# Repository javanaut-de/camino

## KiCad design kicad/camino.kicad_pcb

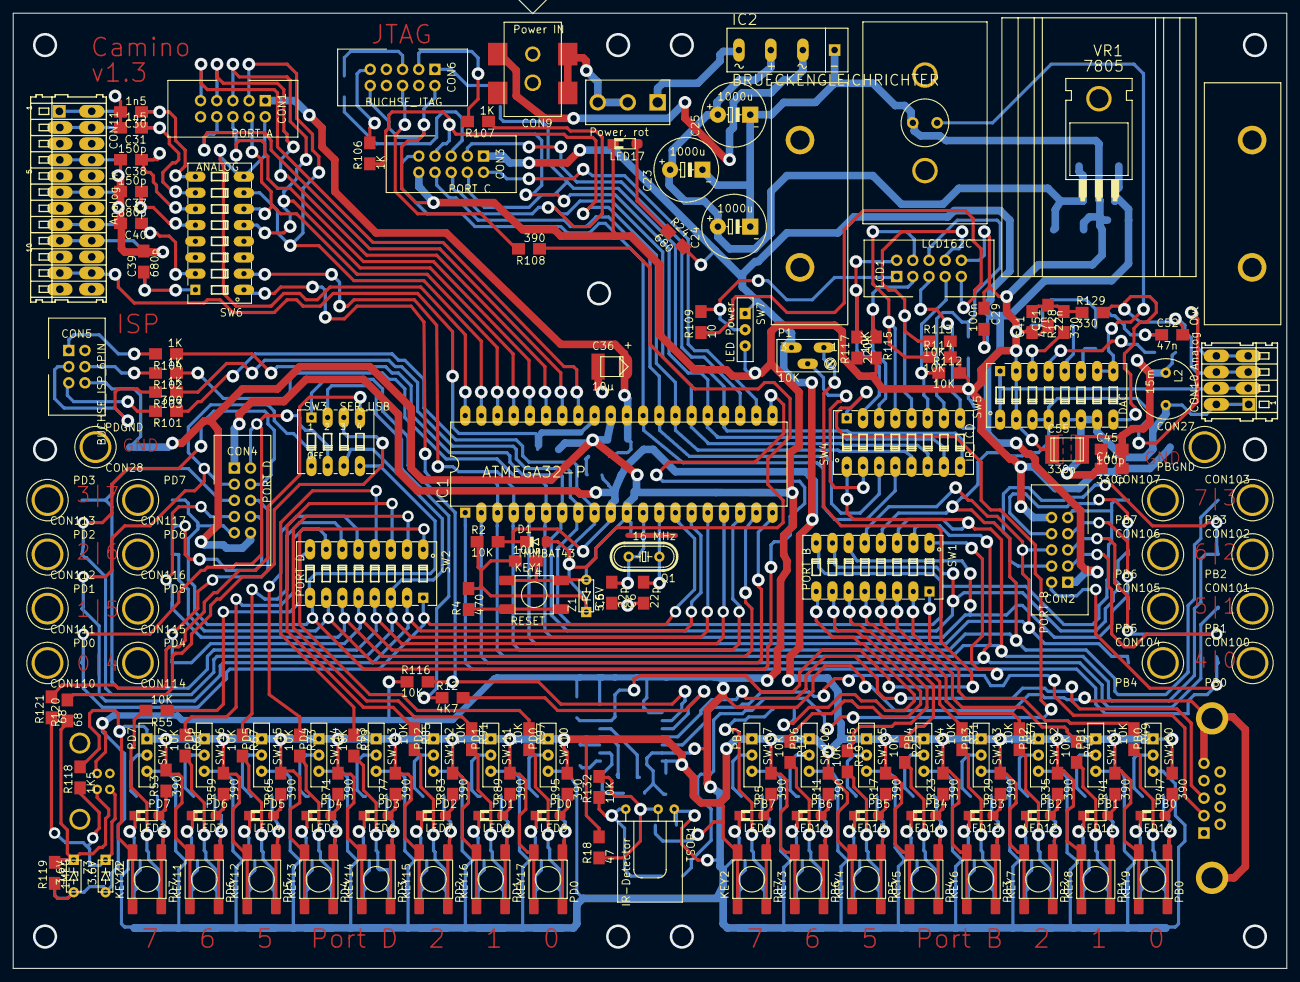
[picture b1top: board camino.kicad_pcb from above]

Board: 2 copper layers, 200.0 x 150.0 mm, 306 parts (0 on the bottom side), 216 nets.

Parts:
C1, C2, C3, C4, C26, C28, C29, C32, C33, C34, C35, C47: 100n; KONDENSATOR_SMD_1206
C5, C6: 22p; KONDENSATOR_SMD_1206
C7, C8, C9, C10, C11, C12, C13, C14, C15, C16, C17, C18, C19, C20, C21, C22: 220n; KONDENSATOR_SMD_1206
C23, C24, C25: 1000u; ELKO_RADIAL_11MM
C27, C46, C55: 330n; KONDENSATOR_SMD_1812
C30, C31: 1n5; KONDENSATOR_SMD_1206
C36: 10µ; ELKO_SMD_TM_B
C37, C38: 150p; KONDENSATOR_SMD_1206
C39, C40: 680p; KONDENSATOR_SMD_1206
C41, C52: 47n; KONDENSATOR_SMD_1206
C42, C51: 22n; KONDENSATOR_SMD_1206
C44: 330p; KONDENSATOR_SMD_1206
C45, C49, C50: 100p; KONDENSATOR_SMD_1206
CON1: PORT A; PFOSTENSTIFTLEISTE_10PIN
CON2: PORT B; PFOSTENSTIFTLEISTE_10PIN
CON3: PORT C; PFOSTENSTIFTLEISTE_10PIN
CON4: PORT D; PFOSTENSTIFTLEISTE_10PIN
CON5: BUCHSE_ISP_6PIN; PFOSTENSTIFTLEISTE_6PIN
CON6: BUCHSE_JTAG; PFOSTENSTIFTLEISTE_10PIN
CON7: RS232; BUCHSE_SERIELL_SUBD9_PIN
CON8: BUCHSE_USB_B; BUCHSE_USB_B_PIN
CON9: Power IN; BUCHSE_DC
CON10: Analog Out; KLEMMBUCHSE_WAGO_233_504_4PIN
CON11: Analog In; KLEMMBUCHSE_WAGO_233_512_12PIN
CON27: PBGND; BUCHSE_LABOR_2MM
CON28: PDGND; BUCHSE_LABOR_2MM
CON100: PB0; BUCHSE_LABOR_2MM
CON101: PB1; BUCHSE_LABOR_2MM
CON102: PB2; BUCHSE_LABOR_2MM
CON103: PB3; BUCHSE_LABOR_2MM
CON104: PB4; BUCHSE_LABOR_2MM
CON105: PB5; BUCHSE_LABOR_2MM
CON106: PB6; BUCHSE_LABOR_2MM
CON107: PB7; BUCHSE_LABOR_2MM
CON110: PD0; BUCHSE_LABOR_2MM
CON111: PD1; BUCHSE_LABOR_2MM
CON112: PD2; BUCHSE_LABOR_2MM
CON113: PD3; BUCHSE_LABOR_2MM
CON114: PD4; BUCHSE_LABOR_2MM
CON115: PD5; BUCHSE_LABOR_2MM
CON116: PD6; BUCHSE_LABOR_2MM
CON117: PD7; BUCHSE_LABOR_2MM
D1: TMMBAT43; DIODE_MINIMELF
D2: S4D; DIODE_SMD_DO214AB
IC1: ATMEGA32-P; DIL40
IC2: BRUECKENGLEICHRICHTER; GLEICHRICHTER_SIL4
IC3: MAX202SO16L; SO16L
KEY1: RESET; TASTER_LSG1301
KEY2: PB7; TASTER_LSG1301
KEY3: PB6; TASTER_LSG1301
KEY4: PB5; TASTER_LSG1301
KEY5: PB4; TASTER_LSG1301
KEY6: PB3; TASTER_LSG1301
KEY7: PB2; TASTER_LSG1301
KEY8: PB1; TASTER_LSG1301
KEY9: PB0; TASTER_LSG1301
KEY10: PD7; TASTER_LSG1301
KEY11: PD6; TASTER_LSG1301
KEY12: PD5; TASTER_LSG1301
KEY13: PD4; TASTER_LSG1301
KEY14: PD3; TASTER_LSG1301
KEY15: PD2; TASTER_LSG1301
KEY16: PD1; TASTER_LSG1301
KEY17: PD0; TASTER_LSG1301
L1: 10u; SPULE_SMD_1008
L2: 15m; SPULE_RADIAL_200MIL
LCD1: LCD162C; LCD_PULT_162C_BC
LED1: PB7; LED_KINGBRIGHT
LED2: PD7; LED_KINGBRIGHT
LED3: PD6; LED_KINGBRIGHT
LED4: PD5; LED_KINGBRIGHT
LED5: PD4; LED_KINGBRIGHT
LED6: PD3; LED_KINGBRIGHT
LED7: PD2; LED_KINGBRIGHT
LED8: PD1; LED_KINGBRIGHT
LED9: PD0; LED_KINGBRIGHT
LED10: PB0; LED_KINGBRIGHT
LED11: PB1; LED_KINGBRIGHT
LED12: PB2; LED_KINGBRIGHT
LED13: PB3; LED_KINGBRIGHT
LED14: PB4; LED_KINGBRIGHT
LED15: PB5; LED_KINGBRIGHT
LED16: PB6; LED_KINGBRIGHT
LED17: Power, rot; LED_KINGBRIGHT
P1: 10K; 3296Y
Q1: 16 MHz; HC49U
R1: 4R7; WIDERSTAND_SMD_1206
R2, R7, R10, R13, R16, R19, R22, R25, R28, R31, R34, R37, R40, R43, R46, R49, R52, R55, R58, R61, R64, R67, R70, R73, R76, R79, R82, R85, R88, R91, R94, R97, R100, R110, R111, R112, R113, R114, R115, R116, R122, R123, R124, R125, R132: 10K; WIDERSTAND_SMD_1206
R3, R6, R102, R103, R104, R105, R106, R107: 1K; WIDERSTAND_SMD_1206
R4: 470; WIDERSTAND_SMD_1206
R5, R11, R17, R23, R29, R35, R41, R47, R53, R59, R65, R71, R77, R83, R89, R95, R101, R108: 390; WIDERSTAND_SMD_1206
R8, R14, R20, R26, R30, R32, R36, R38, R42, R44, R48, R50, R54, R56, R60, R62, R66, R68, R72, R74, R78, R80, R84, R86, R90, R92, R96, R98, R133, R134, R135, R136: 470K; WIDERSTAND_SMD_1206
R9, R15, R21, R27, R33, R39, R45, R51, R57, R63, R69, R75, R81, R87, R93, R99, R126, R127: 100K; WIDERSTAND_SMD_1206
R12: 4K7; WIDERSTAND_SMD_1206
R18: 47; WIDERSTAND_SMD_1206
R24: 680; WIDERSTAND_SMD_1206
R109: 10; WIDERSTAND_SMD_1206
R117: 220K; WIDERSTAND_SMD_1206
R118: 1K5; WIDERSTAND_SMD_1206
R119: 1MEG; WIDERSTAND_SMD_1206
R120, R121: 68; WIDERSTAND_SMD_1206
R128, R129, R130, R131: 330; WIDERSTAND_SMD_1206
SPK1: LAUTSPRECHER; LAUTSPRECHER_BOX
SW1: PORT B; SCHALTER_DIP8
SW2: PORT D; SCHALTER_DIP8
SW3: SER_USB; SCHALTER_DIP4
SW4: IR_LCD; SCHALTER_DIP8
SW5: DAC; SCHALTER_DIP8
SW6: ANALOG; SCHALTER_DIP8
SW7: LED Power; SCHALTER_1UM_ESP
SW23: MAIN; SCHALTER_KNITTER
SW100: PB0; SCHALTER_1UM_ESP
SW101: PB1; SCHALTER_1UM_ESP
SW102: PB2; SCHALTER_1UM_ESP
SW103: PB3; SCHALTER_1UM_ESP
SW104: PB4; SCHALTER_1UM_ESP
SW105: PB5; SCHALTER_1UM_ESP
SW106: PB6; SCHALTER_1UM_ESP
SW107: PB7; SCHALTER_1UM_ESP
SW110: PD0; SCHALTER_1UM_ESP
SW111: PD1; SCHALTER_1UM_ESP
SW112: PD2; SCHALTER_1UM_ESP
SW113: PD3; SCHALTER_1UM_ESP
SW114: PD4; SCHALTER_1UM_ESP
SW115: PD5; SCHALTER_1UM_ESP
SW116: PD6; SCHALTER_1UM_ESP
SW117: PD7; SCHALTER_1UM_ESP
T1, T2, T3, T4, T5, T6, T7, T8, T9, T10, T11, T12, T13, T14, T15, T16: IRLML2502; SOT-23
TSOP1: IR-Detector; RECEIVER_TSOP_LIEGEND
VR1: 7805; TO220_LIEGEND_KUEHLKOERPER_STRANG
Z1: 5,6V; ZENER_PIN_200MIL
Z2, Z3: 3.6V; ZENER_PIN_200MIL

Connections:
/RESET: C4.2, D1.A, IC1.9, R2.1, R4.2, R101.1, R108.1, Z1.K
AVCC: C3.2, C36.POS, CON1.P$1, IC1.30, R1.1
GND: C1.1, C2.2, C3.1, C4.1, C5.1, C6.1, C7.1, C8.1, C9.1, C10.1, C11.1, C12.1, C13.1, C14.1, C15.1, C16.1, C17.1, C18.1, C19.1, C20.1, C21.1, C22.1, C23.-, C24.-, C25.-, C26.1, C27.1, C28.1, C29.1, C30.2, C31.2, C34.2, C35.2, C36.NEG, C37.2, C38.2, C39.2, C40.2, C41.1, C42.1, C46.1, C47.1, C49.1, C50.1, C51.1, C52.1, C55.2, CON1.P$10, CON2.P$10, CON3.P$10, CON4.P$10, CON5.P$6, CON6.P$2, CON6.P$10, CON7.5, CON7.G1, CON7.G2, CON8.GND, CON10.A2, CON10.B2, CON11.A3, CON11.A5, CON11.A7, CON11.A10, CON11.A12, CON11.B3, CON11.B5, CON11.B7, CON11.B10, CON11.B12, CON27.PAD, CON28.PAD, IC1.11, IC1.31, IC2.NEG, IC3.8, IC3.10, KEY1.P$1, KEY1.P$2, LCD1.GND, LED17.K, R8.1, R14.1, R20.1, R26.1, R32.1, R38.1, R44.1, R50.1, R56.1, R62.1, R68.1, R74.1, R80.1, R86.1, R92.1, R98.1, R110.2, R111.2, R112.2, R113.2, R114.2, R115.2, R116.1, R117.1, R119.1, R131.1, SPK1.1, SW5.1, SW5.2, SW5.15, SW5.16, SW6.3, SW6.4, SW6.13, SW6.14, SW7.OFF, SW100.OFF, SW101.OFF, SW102.OFF, SW103.OFF, SW104.OFF, SW105.OFF, SW106.OFF, SW107.OFF, SW110.OFF, SW111.OFF, SW112.OFF, SW113.OFF, SW114.OFF, SW115.OFF, SW116.OFF, SW117.OFF, T1.P$2, T2.P$2, T3.P$2, T4.P$2, T5.P$2, T6.P$2, T7.P$2, T8.P$2, T9.P$2, T10.P$2, T11.P$2, T12.P$2, T13.P$2, T14.P$2, T15.P$2, T16.P$2, TSOP1.GND, VR1.2, Z1.A, Z2.A, Z3.A
unnamed: C1.2, CON11.A11, CON11.B11, IC1.32
unnamed: C5.2, IC1.12, Q1.2
unnamed: C6.2, IC1.13, Q1.1
unnamed: C7.2, R7.2, R9.2, R36.2
unnamed: C8.2, R13.2, R15.2, R42.2
unnamed: C9.2, R19.2, R21.2, R48.2
unnamed: C10.2, R25.2, R27.2, R54.2
unnamed: C11.2, R31.2, R33.2, R60.2
unnamed: C12.2, R37.2, R39.2, R66.2
unnamed: C13.2, R43.2, R45.2, R72.2
unnamed: C14.2, R49.2, R51.2, R78.2
unnamed: C15.2, R55.2, R57.2, R136.2
unnamed: C16.2, R61.2, R63.2, R135.2
unnamed: C17.2, R67.2, R69.2, R134.2
unnamed: C18.2, R73.2, R75.2, R133.2
unnamed: C19.2, R30.1, R79.2, R81.2
unnamed: C20.2, R85.2, R87.2, R96.2
unnamed: C21.2, R90.2, R91.2, R93.2
unnamed: C22.2, R84.2, R97.2, R99.2
unnamed: C23.+, C24.+, C25.+, C27.2, D2.K, IC2.POS, VR1.1
unnamed: C30.1, R127.1, SW6.9
unnamed: C31.1, R126.1, SW6.10
unnamed: C32.1, IC3.1
unnamed: C32.2, IC3.3
unnamed: C33.1, IC3.4
unnamed: C33.2, IC3.5
unnamed: C34.1, IC3.2
unnamed: C35.1, IC3.6, P1.A
unnamed: C37.1, R124.1, SW6.12
unnamed: C38.1, R125.1, SW6.11
unnamed: C39.1, R122.1, SW6.16
unnamed: C40.1, R123.1, SW6.15
unnamed: C41.2, C51.2, R128.2, R129.1
unnamed: C42.2, C52.2, CON10.A3, CON10.B3, R129.2, SW5.8
unnamed: C44.1, C45.1, CON10.A1, CON10.B1, L2.P$2, SW5.5, SW5.6, SW5.7
unnamed: C44.2, C45.2, C55.1, L2.P$1, R130.2
unnamed: C46.2, SW5.12
unnamed: C49.2, CON8.D-, R118.1, R121.1, Z2.K
unnamed: C50.2, CON8.D+, R119.2, R120.1, Z3.K
unnamed: CON1.P$2, IC1.40, SW6.8
unnamed: CON1.P$3, IC1.39, SW6.7
unnamed: CON1.P$4, IC1.38, SW6.6
unnamed: CON1.P$5, IC1.37, SW6.5
unnamed: CON1.P$6, IC1.36
unnamed: CON1.P$7, IC1.35
unnamed: CON1.P$8, IC1.34
unnamed: CON1.P$9, IC1.33
unnamed: CON3.P$2, IC1.22
unnamed: CON3.P$3, IC1.23
unnamed: CON3.P$4, IC1.24, R105.1, SW4.8
unnamed: CON3.P$5, IC1.25, R3.1, SW4.7
unnamed: CON3.P$6, IC1.26, R107.1, SW4.6
unnamed: CON3.P$7, IC1.27, R106.1, SW4.5
unnamed: CON3.P$8, IC1.28, SW4.3
unnamed: CON3.P$9, IC1.29, SW4.4
unnamed: CON5.P$1, R104.2
unnamed: CON5.P$3, R103.2
unnamed: CON5.P$4, R102.2
unnamed: CON5.P$5, R101.2
unnamed: CON6.P$1, R105.2
unnamed: CON6.P$3, R107.2
unnamed: CON6.P$5, R3.2
unnamed: CON6.P$6, R108.2
unnamed: CON6.P$9, R106.2
unnamed: CON7.2, IC3.14
unnamed: CON7.3, IC3.13
unnamed: CON9.FEDER, IC2.AC2
unnamed: CON9.STIFT_A, CON9.STIFT_B, SW23.OFF, SW23.SW
unnamed: CON2.P$5, CON10.A4, CON10.B4, CON103.PAD, IC1.4, SW1.4, SW5.3, SW5.4, SW6.2
unnamed: CON11.A1, CON11.B1, R127.2
unnamed: CON11.A2, CON11.B2, R126.2
unnamed: CON11.A4, CON11.B4, R125.2
unnamed: CON11.A6, CON11.B6, R124.2
unnamed: CON11.A8, CON11.B8, R123.2
unnamed: CON11.A9, CON11.B9, R122.2
unnamed: CON2.P$2, CON100.PAD, IC1.1, SW1.1
unnamed: CON2.P$3, CON101.PAD, IC1.2, SW1.2
unnamed: CON2.P$4, CON102.PAD, IC1.3, SW1.3, SW4.1, SW6.1
unnamed: CON2.P$6, CON104.PAD, IC1.5, SW1.5
unnamed: CON2.P$7, CON105.PAD, IC1.6, R102.1, SW1.6
unnamed: CON2.P$8, CON106.PAD, IC1.7, R104.1, SW1.7
unnamed: CON2.P$9, CON107.PAD, IC1.8, R103.1, SW1.8
unnamed: CON4.P$2, CON110.PAD, IC1.14, SW2.16, SW3.2
unnamed: CON4.P$3, CON111.PAD, IC1.15, SW2.15, SW3.1
unnamed: CON4.P$4, CON112.PAD, IC1.16, SW2.14, SW3.3
unnamed: CON4.P$5, CON113.PAD, IC1.17, SW2.13
unnamed: CON4.P$6, CON114.PAD, IC1.18, SW2.12
unnamed: CON4.P$7, CON115.PAD, IC1.19, SW2.11
unnamed: CON4.P$8, CON116.PAD, IC1.20, SW2.10
unnamed: CON4.P$9, CON117.PAD, IC1.21, SW2.9, SW3.4
unnamed: IC2.AC1, SW23.ON
unnamed: IC3.11, R116.2, SW3.8
unnamed: IC3.12, R12.2
unnamed: KEY1.P$3, KEY1.P$4, R4.1
unnamed: KEY2.P$3, KEY2.P$4, R9.1, R10.2
unnamed: KEY3.P$3, KEY3.P$4, R15.1, R16.2
unnamed: KEY4.P$3, KEY4.P$4, R21.1, R22.2
unnamed: KEY5.P$3, KEY5.P$4, R27.1, R28.2
unnamed: KEY6.P$3, KEY6.P$4, R33.1, R34.2
unnamed: KEY7.P$3, KEY7.P$4, R39.1, R40.2
unnamed: KEY8.P$3, KEY8.P$4, R45.1, R46.2
unnamed: KEY9.P$3, KEY9.P$4, R51.1, R52.2
unnamed: KEY10.P$3, KEY10.P$4, R57.1, R58.2
unnamed: KEY11.P$3, KEY11.P$4, R63.1, R64.2
unnamed: KEY12.P$3, KEY12.P$4, R69.1, R70.2
unnamed: KEY13.P$3, KEY13.P$4, R75.1, R76.2
unnamed: KEY14.P$3, KEY14.P$4, R81.1, R82.2
unnamed: KEY15.P$3, KEY15.P$4, R87.1, R88.2
unnamed: KEY16.P$3, KEY16.P$4, R93.1, R94.2
unnamed: KEY17.P$3, KEY17.P$4, R99.1, R100.2
unnamed: L1.P$1, R1.2
unnamed: LCD1.DB0, R110.1, SW4.9
unnamed: LCD1.DB1, R111.1, SW4.10
unnamed: LCD1.DB2, R112.1, SW4.11
unnamed: LCD1.DB3, R113.1, SW4.12
unnamed: LCD1.E, R114.1, SW4.13
unnamed: LCD1.RS, R115.1, SW4.14
unnamed: LCD1.VCC, R109.2, SW7.SLIDER
unnamed: LCD1.VCON, R117.2, SW4.15
unnamed: LCD1.VLED, R109.1
unnamed: LED1.A, R5.1
unnamed: LED1.K, T1.P$3
unnamed: LED2.A, R53.1
unnamed: LED2.K, T9.P$3
unnamed: LED3.A, R59.1
unnamed: LED3.K, T10.P$3
unnamed: LED4.A, R65.1
unnamed: LED4.K, T11.P$3
unnamed: LED5.A, R71.1
unnamed: LED5.K, T12.P$3
unnamed: LED6.A, R77.1
unnamed: LED6.K, T13.P$3
unnamed: LED7.A, R83.1
unnamed: LED7.K, T14.P$3
unnamed: LED8.A, R89.1
unnamed: LED8.K, T15.P$3
unnamed: LED9.A, R95.1
unnamed: LED9.K, T16.P$3
unnamed: LED10.A, R47.1
unnamed: LED10.K, T8.P$3
unnamed: LED11.A, R41.1
unnamed: LED11.K, T7.P$3
unnamed: LED12.A, R35.1
unnamed: LED12.K, T6.P$3
unnamed: LED13.A, R29.1
unnamed: LED13.K, T5.P$3
unnamed: LED14.A, R23.1
unnamed: LED14.K, T4.P$3
unnamed: LED15.A, R17.1
unnamed: LED15.K, T3.P$3
unnamed: LED16.A, R11.1
unnamed: LED16.K, T2.P$3
unnamed: LED17.A, R24.1
unnamed: P1.S, SW4.2
unnamed: R6.2, SW4.16
unnamed: R7.1, SW1.9
unnamed: R10.1, SW107.SLIDER
unnamed: R12.1, SW3.7
unnamed: R13.1, SW1.10
unnamed: R14.2, R42.1, T2.P$1
unnamed: R16.1, SW106.SLIDER
unnamed: R19.1, SW1.11
unnamed: R20.2, R48.1, T3.P$1
unnamed: R22.1, SW105.SLIDER
unnamed: R25.1, SW1.12
unnamed: R26.2, R54.1, T4.P$1
unnamed: R28.1, SW104.SLIDER
unnamed: R30.2, R80.2, T13.P$1
unnamed: R31.1, SW1.13
unnamed: R32.2, R60.1, T5.P$1
unnamed: R34.1, SW103.SLIDER
unnamed: R8.2, R36.1, T1.P$1
unnamed: R37.1, SW1.14
unnamed: R38.2, R66.1, T6.P$1
unnamed: R40.1, SW102.SLIDER
unnamed: R43.1, SW1.15
unnamed: R44.2, R72.1, T7.P$1
unnamed: R46.1, SW101.SLIDER
unnamed: R49.1, SW1.16
unnamed: R50.2, R78.1, T8.P$1
unnamed: R52.1, SW100.SLIDER
unnamed: R55.1, SW2.8
unnamed: R58.1, SW117.SLIDER
unnamed: R61.1, SW2.7
unnamed: R64.1, SW116.SLIDER
unnamed: R67.1, SW2.6
unnamed: R70.1, SW115.SLIDER
unnamed: R73.1, SW2.5
unnamed: R76.1, SW114.SLIDER
unnamed: R79.1, SW2.4
unnamed: R82.1, SW113.SLIDER
unnamed: R84.1, R98.2, T16.P$1
unnamed: R85.1, SW2.3
unnamed: R86.2, R96.1, T14.P$1
unnamed: R88.1, SW112.SLIDER
unnamed: R90.1, R92.2, T15.P$1
unnamed: R91.1, SW2.2
unnamed: R94.1, SW111.SLIDER
unnamed: R97.1, SW2.1
unnamed: R100.1, SW110.SLIDER
unnamed: R120.2, SW3.6
unnamed: R121.2, SW3.5
unnamed: R128.1, SW5.14
unnamed: R130.1, SW5.13
unnamed: R131.2, SW5.11
unnamed: R6.1, R132.1, TSOP1.OUT
unnamed: R18.1, R132.2, TSOP1.VS
unnamed: R74.2, R133.1, T12.P$1
unnamed: R68.2, R134.1, T11.P$1
unnamed: R62.2, R135.1, T10.P$1
unnamed: R56.2, R136.1, T9.P$1
unnamed: SPK1.2, SW5.9, SW5.10
VCC: C2.1, C26.2, C28.2, C29.2, C47.2, CON2.P$1, CON3.P$1, CON4.P$1, D1.K, D2.A, IC1.10, KEY2.P$1, KEY2.P$2, KEY3.P$1, KEY3.P$2, KEY4.P$1, KEY4.P$2, KEY5.P$1, KEY5.P$2, KEY6.P$1, KEY6.P$2, KEY7.P$1, KEY7.P$2, KEY8.P$1, KEY8.P$2, KEY9.P$1, KEY9.P$2, KEY10.P$1, KEY10.P$2, KEY11.P$1, KEY11.P$2, KEY12.P$1, KEY12.P$2, KEY13.P$1, KEY13.P$2, KEY14.P$1, KEY14.P$2, KEY15.P$1, KEY15.P$2, KEY16.P$1, KEY16.P$2, KEY17.P$1, KEY17.P$2, L1.P$2, P1.E, R2.2, R5.2, R11.2, R17.2, R18.2, R23.2, R24.2, R29.2, R35.2, R41.2, R47.2, R53.2, R59.2, R65.2, R71.2, R77.2, R83.2, R89.2, R95.2, R118.2, SW7.ON, SW100.ON, SW101.ON, SW102.ON, SW103.ON, SW104.ON, SW105.ON, SW106.ON, SW107.ON, SW110.ON, SW111.ON, SW112.ON, SW113.ON, SW114.ON, SW115.ON, SW116.ON, SW117.ON, VR1.3

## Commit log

2020-07-20 Initial for publish
